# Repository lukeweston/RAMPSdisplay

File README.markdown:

v1.1: No SD card or thermocouples. Very simple, low-density, "agricultural" PCB layout, which can easily be made single-sided and is well suited to DIY PCB fabrication. Even inexperienced persons should be able to easily make a working board, using photolithography, toner transfer, or CNC milling techniques.

v1.2: "Official" production version. Includes three thermocouple interfaces and micro-SD card. Micro-SD card socket is the Amphenol 101-00660-68-6.

v1.3: Changed to the same micro-SD card PCB footprint as the Kliment SDRamps board, using some generic micro-SD card socket from eBay.
Also changed to self-oscillating through-hole buzzer, removed buzzer drive oscillator, and reduced prototyping hole number to keep total drill hits less than 300.

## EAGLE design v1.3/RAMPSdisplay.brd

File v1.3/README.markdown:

v1.3: Changed to the same micro-SD card PCB footprint as the Kliment SDRamps board, using some generic micro-SD card socket from eBay.
Also changed to self-oscillating through-hole buzzer, removed buzzer drive oscillator, and reduced prototyping hole number to keep total drill hits less than 300.

Pinout: The pinout takes the 20-way cable from the display board (IDC header plug) and splits it in half, with 13 wires going to 13 contiguous pins on the 18-way single-row
expansion header on the edge of the RAMPS board, and 7 wires going to an 8-pin dual-row IDC header plug which connects to the SPI header. So you can just take a 13-way
single-row 0.1" IDC ribbon cable header plug and a 8-pin dual-row 0.1" IDC ribbon cable header plug and just crimp them on and plug them straight on without any crossovers or
the like.

Note that the 8th pin on the SPI header plug is not connected to the cable.

This is the pinout for the 20-pin (dual-row) IDC ribbon cable header on the display board:

1: RS (Pin 18 on 18-pin RAMPS expansion header, Arduino pin 16)  
2: EN (Pin 17 on 18-pin RAMPS expansion header, Arduino pin 17)  
3: D4 (Pin 16 on 18-pin RAMPS expansion header, Arduino pin 23)  
4: D5 (Pin 15 on 18-pin RAMPS expansion header, Arduino pin 25)  
5: D6 (Pin 14 on 18-pin RAMPS expansion header, Arduino pin 27)  
6: D7 (Pin 13 on 18-pin RAMPS expansion header, Arduino pin 29)  
7: Sw (Pin 12 on 18-pin RAMPS expansion header, Arduino pin 31)  
8: Buzzer (Pin 11 on 18-pin RAMPS expansion header, Arduino pin 33)  
9: Encoder A (Pin 10 on 18-pin RAMPS expansion header, Arduino pin 35)  
10: Encoder B (Pin 9 on 18-pin RAMPS expansion header, Arduino pin 37)  
11: Backlight (Pin 8 on 18-pin RAMPS expansion header, Arduino pin 38)  
12: TC2 (Pin 7 on 18-pin RAMPS expansion header, Arduino pin 41)  
13: TC3 (Pin 6 on 18-pin RAMPS expansion header, Arduino pin 43)  

14: +5V (Pin 1 on RAMPS 8-pin SPI header, 8x2 IDC header plug)  
15: SD CS (Pin 2 on RAMPS SPI header, Arduino pin 49)  
16: MISO (Pin 3 on RAMPS SPI header, Arduino pin 50)  
17: MOSI (Pin 4 on RAMPS SPI header, Arduino pin 51)  
18: SCK (Pin 5 on RAMPS SPI header, Arduino pin 52)  
19: TC1 CS (Pin 6 on RAMPS SPI header, Arduino pin 53)  
20: Gnd (Pin 7 on RAMPS SPI header)

(Note: Pin 8 on 8-pin IDC header plug is not connected.)

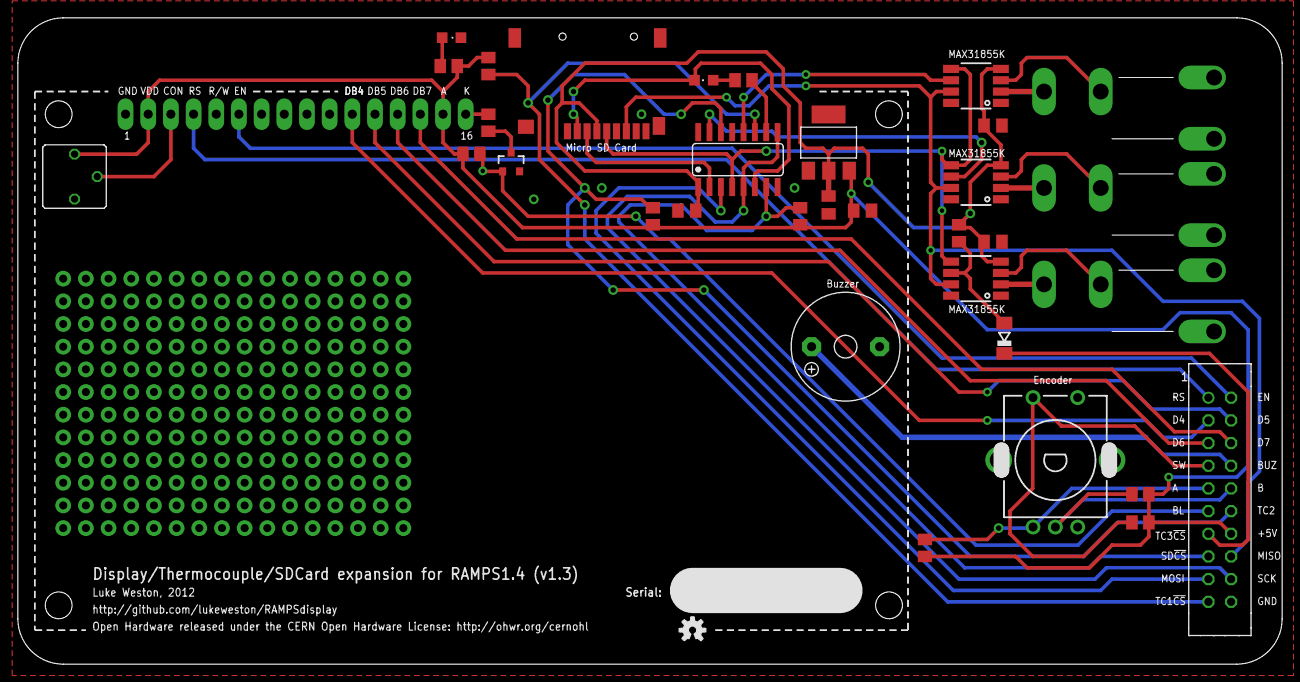
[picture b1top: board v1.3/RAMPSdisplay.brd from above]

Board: 2 copper layers, 141.6 x 72.4 mm, 35 parts (0 on the bottom side), 39 nets.

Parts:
C1, C3, C4: 100n; C0805K
C2: 10uF; C0805K
C5: 100 nF; C0805K
D1: LL4148; SOD80C
IC1: LD1117; SOT223
IC2: HEF4050B; SO16
IC3, IC4, IC5: MAX31855K; MCLENG_SOIC-8
J1, J2, J5: PCC-SMP-V-K; MCLAUGHLINENG_TC_JACK
J3: Micro-SD socket; MICROSD_PP
J4: Interface; CON20
LCD1: HD44780 20x4; HDM20416L
LED1: Power; CHIPLED_0805
LED2: SD act; CHIPLED_0805
Q1: 2N7002; SOT23-3
Q2: Piezo; F/TMB
R1, R2, R3, R5, R8, R10: 10k; M0805
R4: 22 R; M0805
R6: 1k; M0805
R7, R9, R11: 10 k; M0805
SW1: CI-11
U$: OSHW-LOGOS; OSHW-LOGO-S
VR1: 10 k; CT6

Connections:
!SD_CS: IC2.7, J4.15, R10.1
!TC1_CS: IC2.11, J4.19, R9.1
!TC2_CS: IC2.14, J4.12, R8.1
!TC3_CS: D1.C, J4.13
+3V3: C2.1, C3.1, C4.1, C5.1, IC1.2, IC2.1, IC3.VCC, IC4.VCC, IC5.VCC, J3.4, R11.2
+5V: C1.1, IC1.3, J4.14, LCD1.2, LCD1.15, R1.2, R2.2, R3.2, R5.2, R6.2, R8.2, R9.2, R10.2, VR1.A
A: J4.9, R3.1, SW1.A
B: J4.10, R1.1, SW1.B
BF: IC2.12, IC3.CS
BLIGHT: J4.11, Q1.1, R5.1
BUZZER: J4.8, Q2.+
D4: J4.3, LCD1.11
D5: J4.4, LCD1.12
D6: J4.5, LCD1.13
D7: J4.6, LCD1.14
EN: J4.2, LCD1.6
FOO: IC2.6, J3.2, LED2.C
GND: C1.2, C2.2, C3.2, C4.2, C5.2, IC1.1, IC2.8, IC3.GND, IC4.GND, IC5.GND, J1.P$1, J1.P$2, J2.P$1, J2.P$2, J3.6, J3.GND@1, J3.GND@2, J3.GND@3, J3.GND@4, J4.20, J5.P$1, J5.P$2, LCD1.1, LCD1.5, LED1.C, Q1.2, Q2.-, SW1.C, SW1.E, VR1.E
MISO: IC3.SO, IC4.SO, IC5.SO, J3.7, J4.16
MOSI: IC2.3, J4.17
MOSI_3.3V: IC2.2, J3.3
unnamed: LCD1.3, VR1.S
unnamed: LCD1.16, R4.2
unnamed: IC5.T+, J5.T+
unnamed: IC5.T-, J5.T-
unnamed: Q1.3, R4.1
unnamed: IC4.T-, J2.T-
unnamed: D1.A, IC5.CS, R11.1
unnamed: IC4.T+, J2.T+
unnamed: IC3.T-, J1.T-
unnamed: IC3.T+, J1.T+
unnamed: IC2.15, IC4.CS
unnamed: LED2.A, R7.1
unnamed: IC2.10, R7.2
unnamed: LED1.A, R6.1
RS: J4.1, LCD1.4
SCK: IC2.5, IC2.9, J4.18
SCK_3.3V: IC2.4, IC3.SCK, IC4.SCK, IC5.SCK, J3.5
SW: J4.7, R2.1, SW1.D

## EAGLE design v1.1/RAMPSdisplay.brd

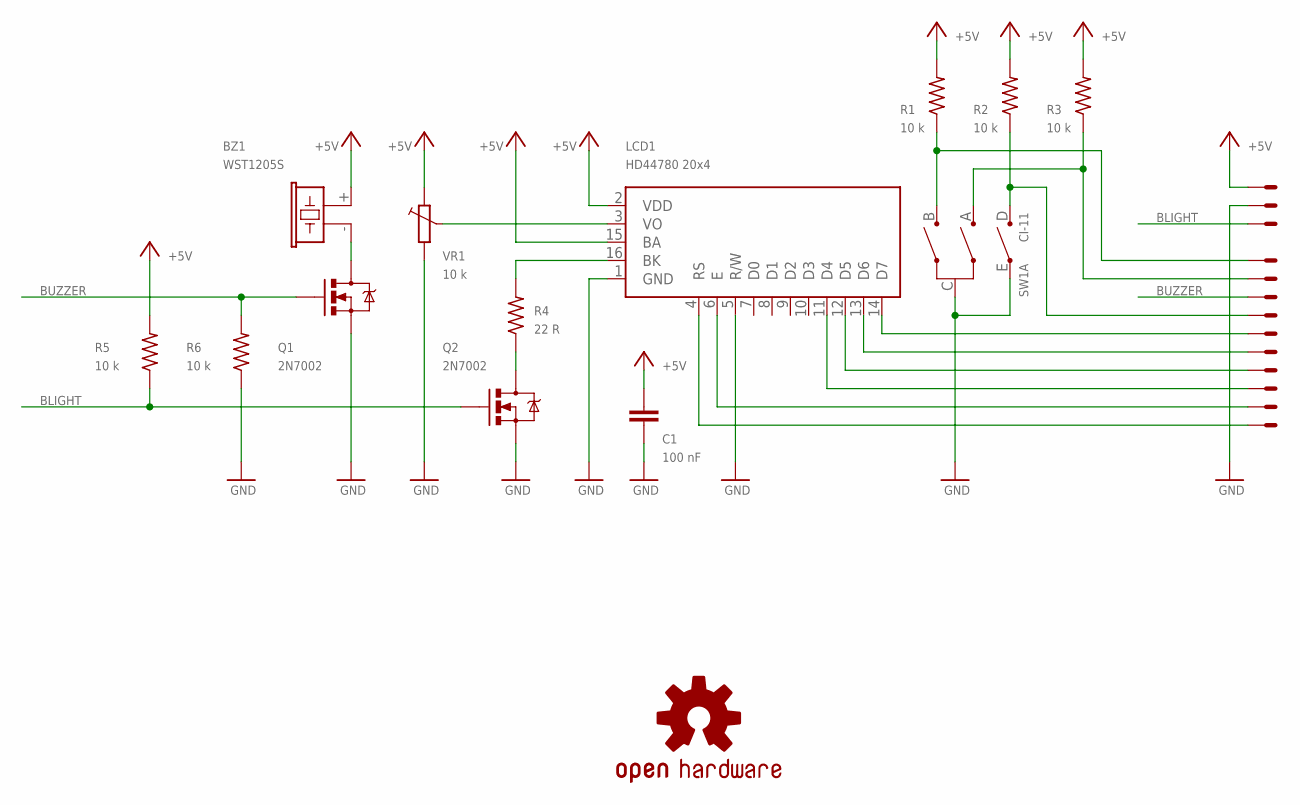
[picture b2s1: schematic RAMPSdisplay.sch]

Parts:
BZ1: WST1205S; F/CM12P
C1: 100 nF; C0805K
J1: 22-05-7038-03; 7395-03
J2: 22-05-7108-10; 7395-10
LCD1: HD44780 20x4; HDM20416L
Q1, Q2: 2N7002; SOT23-3
R1, R2, R3, R5, R6: 10 k; M0805
R4: 22 R; M0805
SW1: CI-11
U$: OSHW-LOGOS; OSHW-LOGO-S
VR1: 10 k; S64W

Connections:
+5V: BZ1.+ (1), C1.1, J1.1, LCD1.2 (VDD), LCD1.15 (BA), R1.2, R2.2, R3.2, R5.2, VR1.E
BLIGHT: J1.3, Q2.1 (G), R5.1
BUZZER: J2.3, Q1.1 (G), R6.2
GND: C1.2, J1.2, LCD1.1 (GND), LCD1.5 (R/W), Q1.2 (S), Q2.2 (S), R6.1, SW1.C, SW1.E, VR1.A
unnamed: LCD1.16 (BK), R4.2
unnamed: J2.4, R2.1, SW1.D
unnamed: J2.5, LCD1.14 (D7)
unnamed: J2.6, LCD1.13 (D6)
unnamed: J2.7, LCD1.12 (D5)
unnamed: J2.8, LCD1.11 (D4)
unnamed: J2.9, LCD1.6 (E)
unnamed: J2.10, LCD1.4 (RS)
unnamed: LCD1.3 (VO), VR1.S
unnamed: J2.2, R3.1, SW1.A
unnamed: J2.1, R1.1, SW1.B
unnamed: Q2.3 (D), R4.1
unnamed: BZ1.- (2), Q1.3 (D)

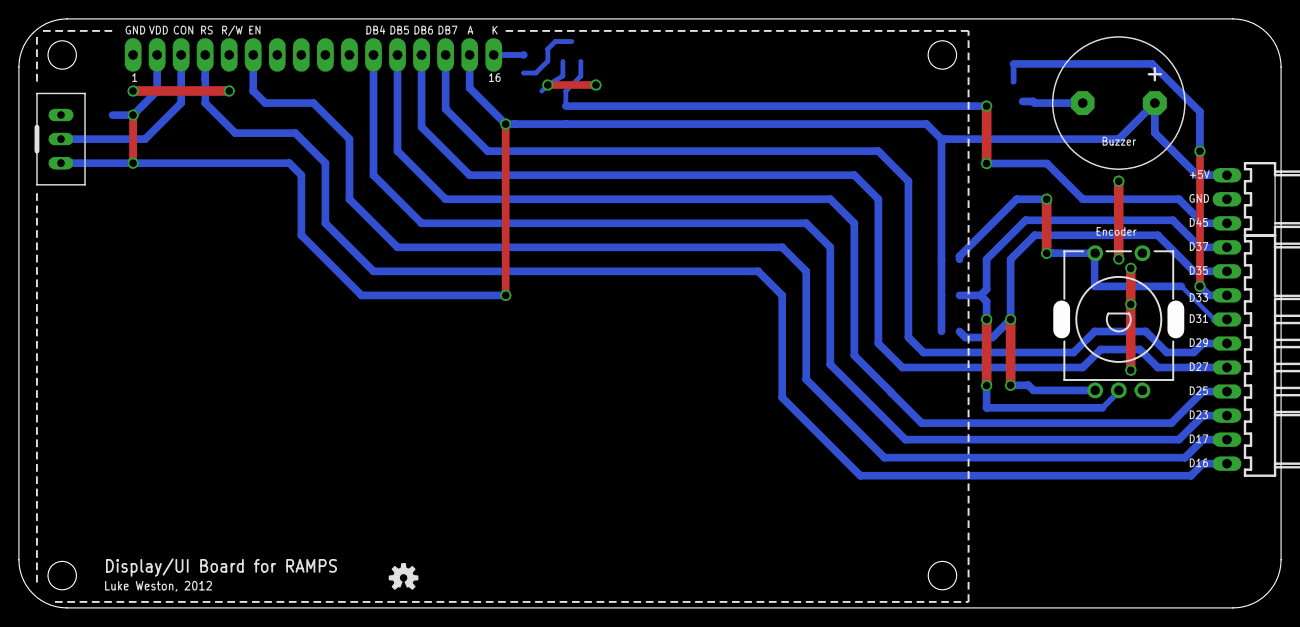
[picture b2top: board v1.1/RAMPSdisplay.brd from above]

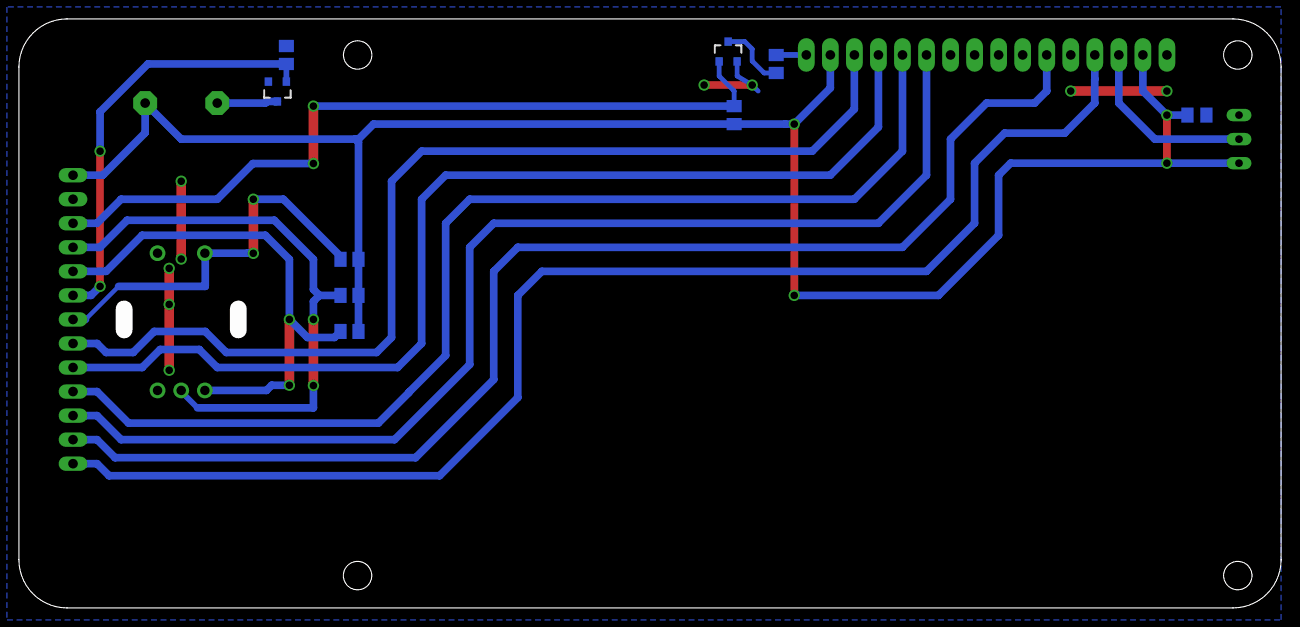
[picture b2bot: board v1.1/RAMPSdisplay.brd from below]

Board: 2 copper layers, 133.4 x 62.2 mm, 16 parts (9 on the bottom side), 17 nets.

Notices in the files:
v1.1/RAMPSdisplay.sch:
Released under CERN Open Hardware License:
v1.3/RAMPSdisplay.brd:
Open Hardware released under the CERN Open Hardware License: http://ohwr.org/cernohl
